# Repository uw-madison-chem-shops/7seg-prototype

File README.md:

# 7seg-prototype

Prototype board for playing with board-mount 7-segment displays.

## Repository

This is an open source hardware project licensed under the CERN Open Hardware Licence Version 2 - Permissive.
Please see the LICENSE file for the complete license.

This repository is being mirrored to several version control systems in an attempt to ensure maximum avaliability.

| name           | url                                                     |
| -------------- | ------------------------------------------------------- | 
| Chem (primary) | https://git.chem.wisc.edu/shop/7seg-prototype           |
| GitHub         | https://github.com/uw-madison-chem-shops/7seg-prototype | 
| GitLab         | https://gitlab.com/uw-madison-chem-shops/7seg-prototype |

## PCB

This PCB was designed using KiCAD version 5.
Refer to `7seg-prototype.pdf` for schematic.
PCB images generated with [tracespace](https://github.com/tracespace/tracespace) follow.

## Bill of Materials

| reference      | value         | manufacturer  | part number          | vendors |
| :------------- | :------------ | :------------ | :------------------- | :------ |
| C1             | 100u, 1206    |               |                      |         |
| C3             | 20 pF         |               |                      |         |
| C4             | 100n, 1206    |               |                      |         |
| D0-D8          | 7seg Chip     | Kingbright    | ACSC08-51SGWA        | [DigiKey](https://www.digikey.com/en/products/detail/kingbright/ACSC02-41SURKWA-F01/2163667) [Newark](https://www.mouser.com/ProductDetail/Kingbright/ACSC02-41SURKWA-F01?qs=%2Fha2pyFaduicALusGN0JMV18ke69tDrFejQJKKPoTyQtUMuwRB9U3sQCvd0zqoH%2F) |
| J1-J5          | Test Point    |               |                      |         |
| R2             | 100k          |               |                      |         |
| U3             | Driver Chip   | Maxim         | MAX6951CEE+          | [DigiKey](https://www.digikey.com/en/products/detail/maxim-integrated/MAX6951CEE-T/5640031) [Newark](https://www.newark.com/maxim-integrated-products/max6951cee/led-driver-smd-8mhz-qsop-16/dp/81Y9572?rpsku=rel1%3AMAX6951CEET) [Mouser](https://www.mouser.com/ProductDetail/?qs=1THa7WoU59G039lytpTsUQ%3D%3D) |

## Firmware

You may find an ino file in the "firmware" folder.
Upload this to an Arduino to make an easy test driver for this prototype.
Wire the prototype board like an SPI peripheral.

## Changelog

### 1.0.0

#### Added
- initial design

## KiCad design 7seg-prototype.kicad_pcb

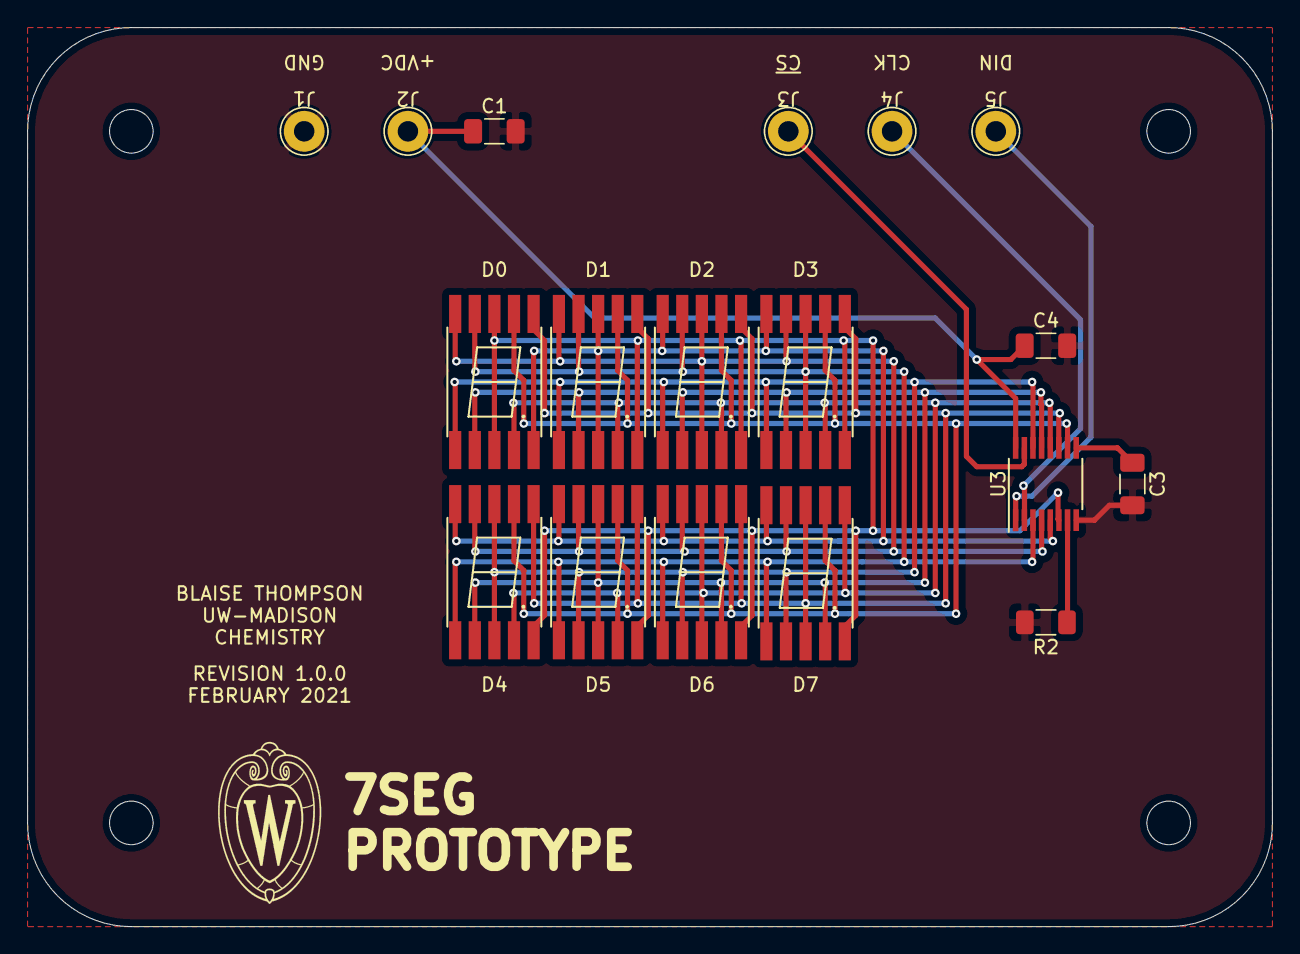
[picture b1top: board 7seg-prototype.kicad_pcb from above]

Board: 2 copper layers, 91.4 x 66.0 mm, 18 parts (0 on the bottom side), 16 nets.

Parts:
C1: 100u; C_1206_3216Metric_Pad1.33x1.80mm_HandSolder
C3: C; C_1206_3216Metric_Pad1.33x1.80mm_HandSolder
C4: 100n; C_1206_3216Metric_Pad1.33x1.80mm_HandSolder
D0, D1, D2, D3, D4, D5, D6, D7: ACSC02-41SURKWA-F01
J1: GND; TestPoint_THTPad_D3.0mm_Drill1.5mm
J2: V+; TestPoint_THTPad_D3.0mm_Drill1.5mm
J3: ~CS~; TestPoint_THTPad_D3.0mm_Drill1.5mm
J4: CLK; TestPoint_THTPad_D3.0mm_Drill1.5mm
J5: DIN; TestPoint_THTPad_D3.0mm_Drill1.5mm
R2: R_US; R_1206_3216Metric_Pad1.30x1.75mm_HandSolder
U3: MAX6951; QSOP-16_3.9x4.9mm_P0.635mm

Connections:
+VDC: C1.1, C4.1, J2.1, U3.16
/SEG0: D0.3, D0.8, D1.5, D2.5, D3.5, D4.5, D5.5, D6.5, D7.5, U3.6
/SEG1: D0.5, D1.3, D1.8, D2.10, D3.10, D4.10, D5.10, D6.10, D7.10, U3.5
/SEG2: D0.10, D1.10, D2.3, D2.8, D3.9, D4.9, D5.9, D6.9, D7.9, U3.4
/SEG3: D0.9, D1.9, D2.9, D3.3, D3.8, D4.1, D5.1, D6.1, D7.1, U3.3
/SEG4: D0.1, D1.1, D2.1, D3.1, D4.3, D4.8, D5.2, D6.2, D7.2, U3.14
/SEG5: D0.2, D1.2, D2.2, D3.2, D4.2, D5.3, D5.8, D6.4, D7.4, U3.13
/SEG6: D0.4, D1.4, D2.4, D3.4, D4.4, D5.4, D6.3, D6.8, D7.6, U3.12
/SEG7: D0.6, D1.6, D2.6, D3.6, D4.6, D5.6, D6.6, D7.3, D7.8, U3.11
/SEG8: D0.7, D1.7, D2.7, D3.7, D4.7, D5.7, D6.7, D7.7, U3.10
GND: C1.2, C3.2, C4.2, J1.1, R2.2, U3.8
unnamed: C3.1, U3.9
unnamed: J3.1, U3.15
unnamed: J4.1, U3.2
unnamed: J5.1, U3.1
unnamed: R2.1, U3.7

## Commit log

2021-02-03 gerber-1.0.0
2021-03-24 license
2021-03-24 sources
2021-03-24 firmware instructions
2021-03-25 restructure
2021-03-25 images as html
2021-03-25 drill
